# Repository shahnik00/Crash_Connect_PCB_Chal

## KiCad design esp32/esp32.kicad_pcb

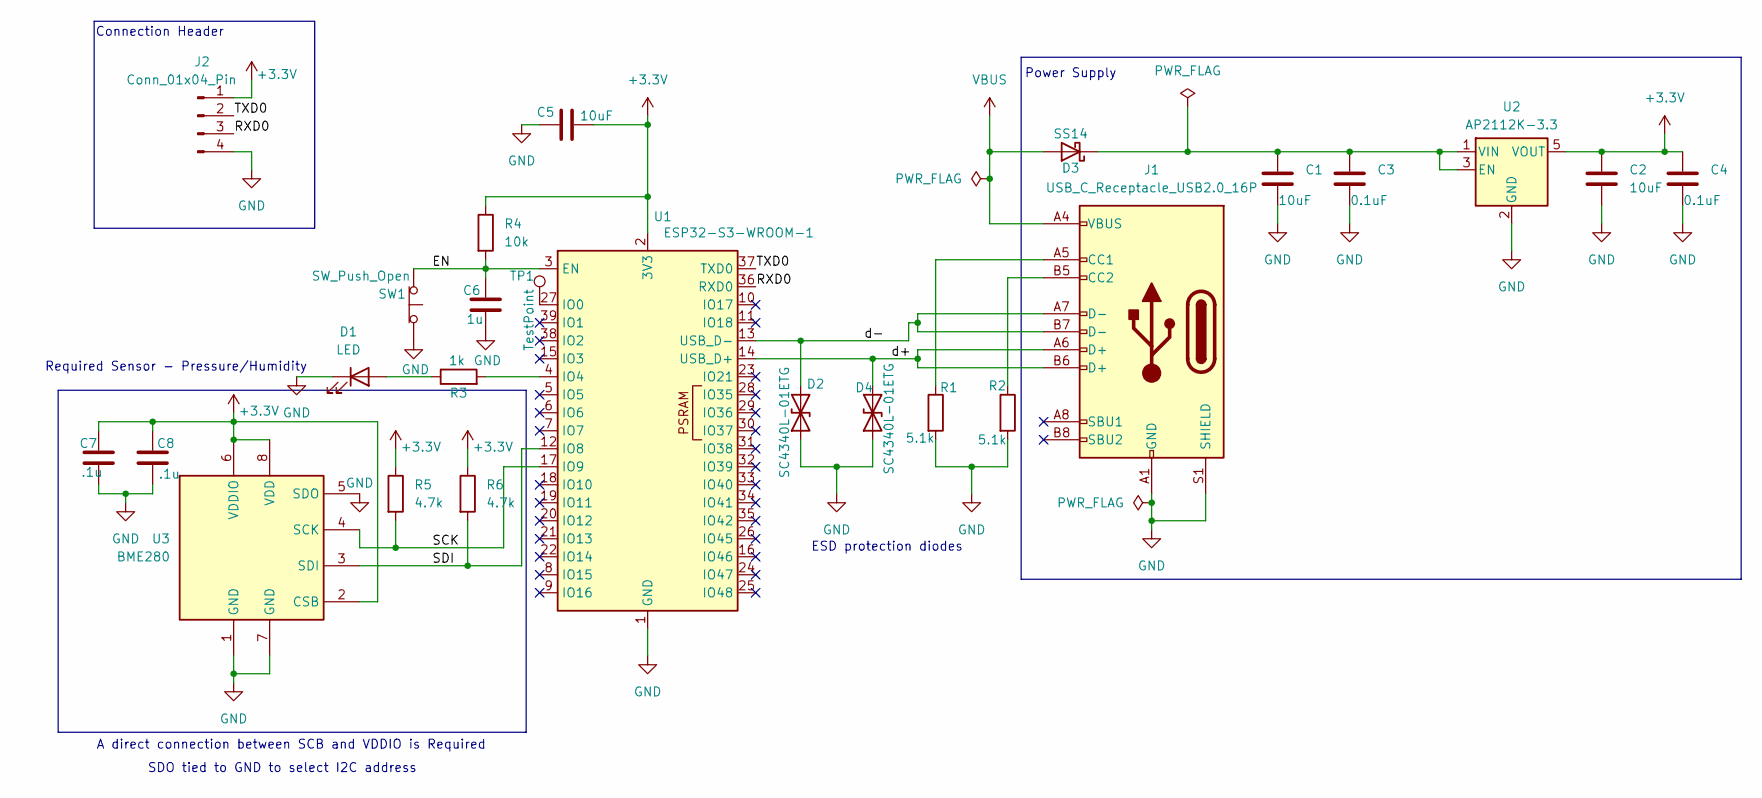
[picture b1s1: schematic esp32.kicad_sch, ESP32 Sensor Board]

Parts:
C1, C2: 10uF; C_0805_2012Metric_Pad1.18x1.45mm_HandSolder
C3, C4: 0.1uF; C_0603_1608Metric_Pad1.08x0.95mm_HandSolder
C5: 10uF; C_0603_1608Metric_Pad1.08x0.95mm_HandSolder
C6: 1u; C_0603_1608Metric_Pad1.08x0.95mm_HandSolder
C7, C8: .1u; C_0603_1608Metric_Pad1.08x0.95mm_HandSolder
D1: LED; LED_0603_1608Metric_Pad1.05x0.95mm_HandSolder
D2, D4: SC4340L-01ETG; D_0603_1608Metric_Pad1.05x0.95mm_HandSolder
D3: SS14; D_SMA
J1: USB_C_Receptacle_USB2.0_16P; USB_C_Receptacle_G-Switch_GT-USB-7010ASV
J2: Conn_01x04_Pin; PinSocket_1x04_P2.54mm_Vertical
R1, R2: 5.1k; R_0603_1608Metric_Pad0.98x0.95mm_HandSolder
R3: 1k; R_0603_1608Metric_Pad0.98x0.95mm_HandSolder
R4: 10k; R_0603_1608Metric_Pad0.98x0.95mm_HandSolder
R5, R6: 4.7k; R_0603_1608Metric_Pad0.98x0.95mm_HandSolder
SW1: SW_Push_Open; SW_Push_1P1T_NO_CK_KMR2
TP1: TestPoint; TestPoint_Keystone_5010-5014_Multipurpose
U1: ESP32-S3-WROOM-1
U2: AP2112K-3.3; SOT-23-5
U3: BME280; Bosch_LGA-8_2.5x2.5mm_P0.65mm_ClockwisePinNumbering

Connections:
+3.3V: C2.1, C4.1, C5.1, C7.1, C8.1, J2.1, R4.1, R5.1, R6.1, U1.2 (3V3), U2.5 (VOUT), U3.2 (CSB), U3.6 (VDDIO), U3.8 (VDD)
/EN: C6.1, R4.2, SW1.1 (A), U1.3 (EN)
/RXD0: J2.3, U1.36 (RXD0)
/SCK: R5.2, U1.17 (IO9), U3.4 (SCK)
/SDI: R6.2, U1.12 (IO8), U3.3 (SDI)
/TXD0: J2.2, U1.37 (TXD0)
/d+: D4.2 (A2), J1.A6 (D+), J1.B6 (D+), U1.14 (USB_D+)
/d-: D2.2 (A2), J1.A7 (D-), J1.B7 (D-), U1.13 (USB_D-)
GND: C1.2, C2.2, C3.2, C4.2, C5.2, C6.2, C7.2, C8.2, D1.1 (K), D2.1 (A1), D4.1 (A1), J1.A1 (GND), J1.A12 (GND), J1.B1 (GND), J1.B12 (GND), J1.S1 (SHIELD), J2.4, R1.2, R2.2, SW1.2 (B), U1.1 (GND), U1.40 (GND), U1.41 (GND), U2.2 (GND), U3.1 (GND), U3.5 (SDO), U3.7 (GND)
unnamed: D1.2 (A), R3.1
unnamed: C1.1, C3.1, D3.1 (K), U2.1 (VIN), U2.3 (EN)
unnamed: J1.A5 (CC1), R1.1
unnamed: J1.B5 (CC2), R2.1
unnamed: TP1.1, U1.27 (IO0)
unnamed: R3.2, U1.4 (IO4)
VBUS: D3.2 (A), J1.A4 (VBUS), J1.A9 (VBUS), J1.B4 (VBUS), J1.B9 (VBUS)

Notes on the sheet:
A direct connection between SCB and VDDIO is Required
Connection Header
ESD protection diodes
Required Sensor - Pressure/Humidity
SDO tied to GND to select I2C address
Power Supply

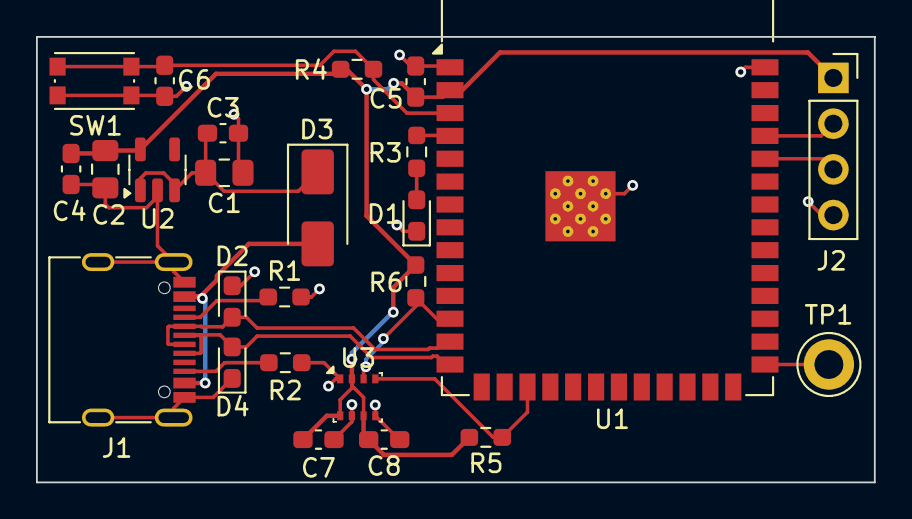
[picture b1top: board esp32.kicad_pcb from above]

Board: 2 copper layers, 46.5 x 24.8 mm, 25 parts (0 on the bottom side), 16 nets.
